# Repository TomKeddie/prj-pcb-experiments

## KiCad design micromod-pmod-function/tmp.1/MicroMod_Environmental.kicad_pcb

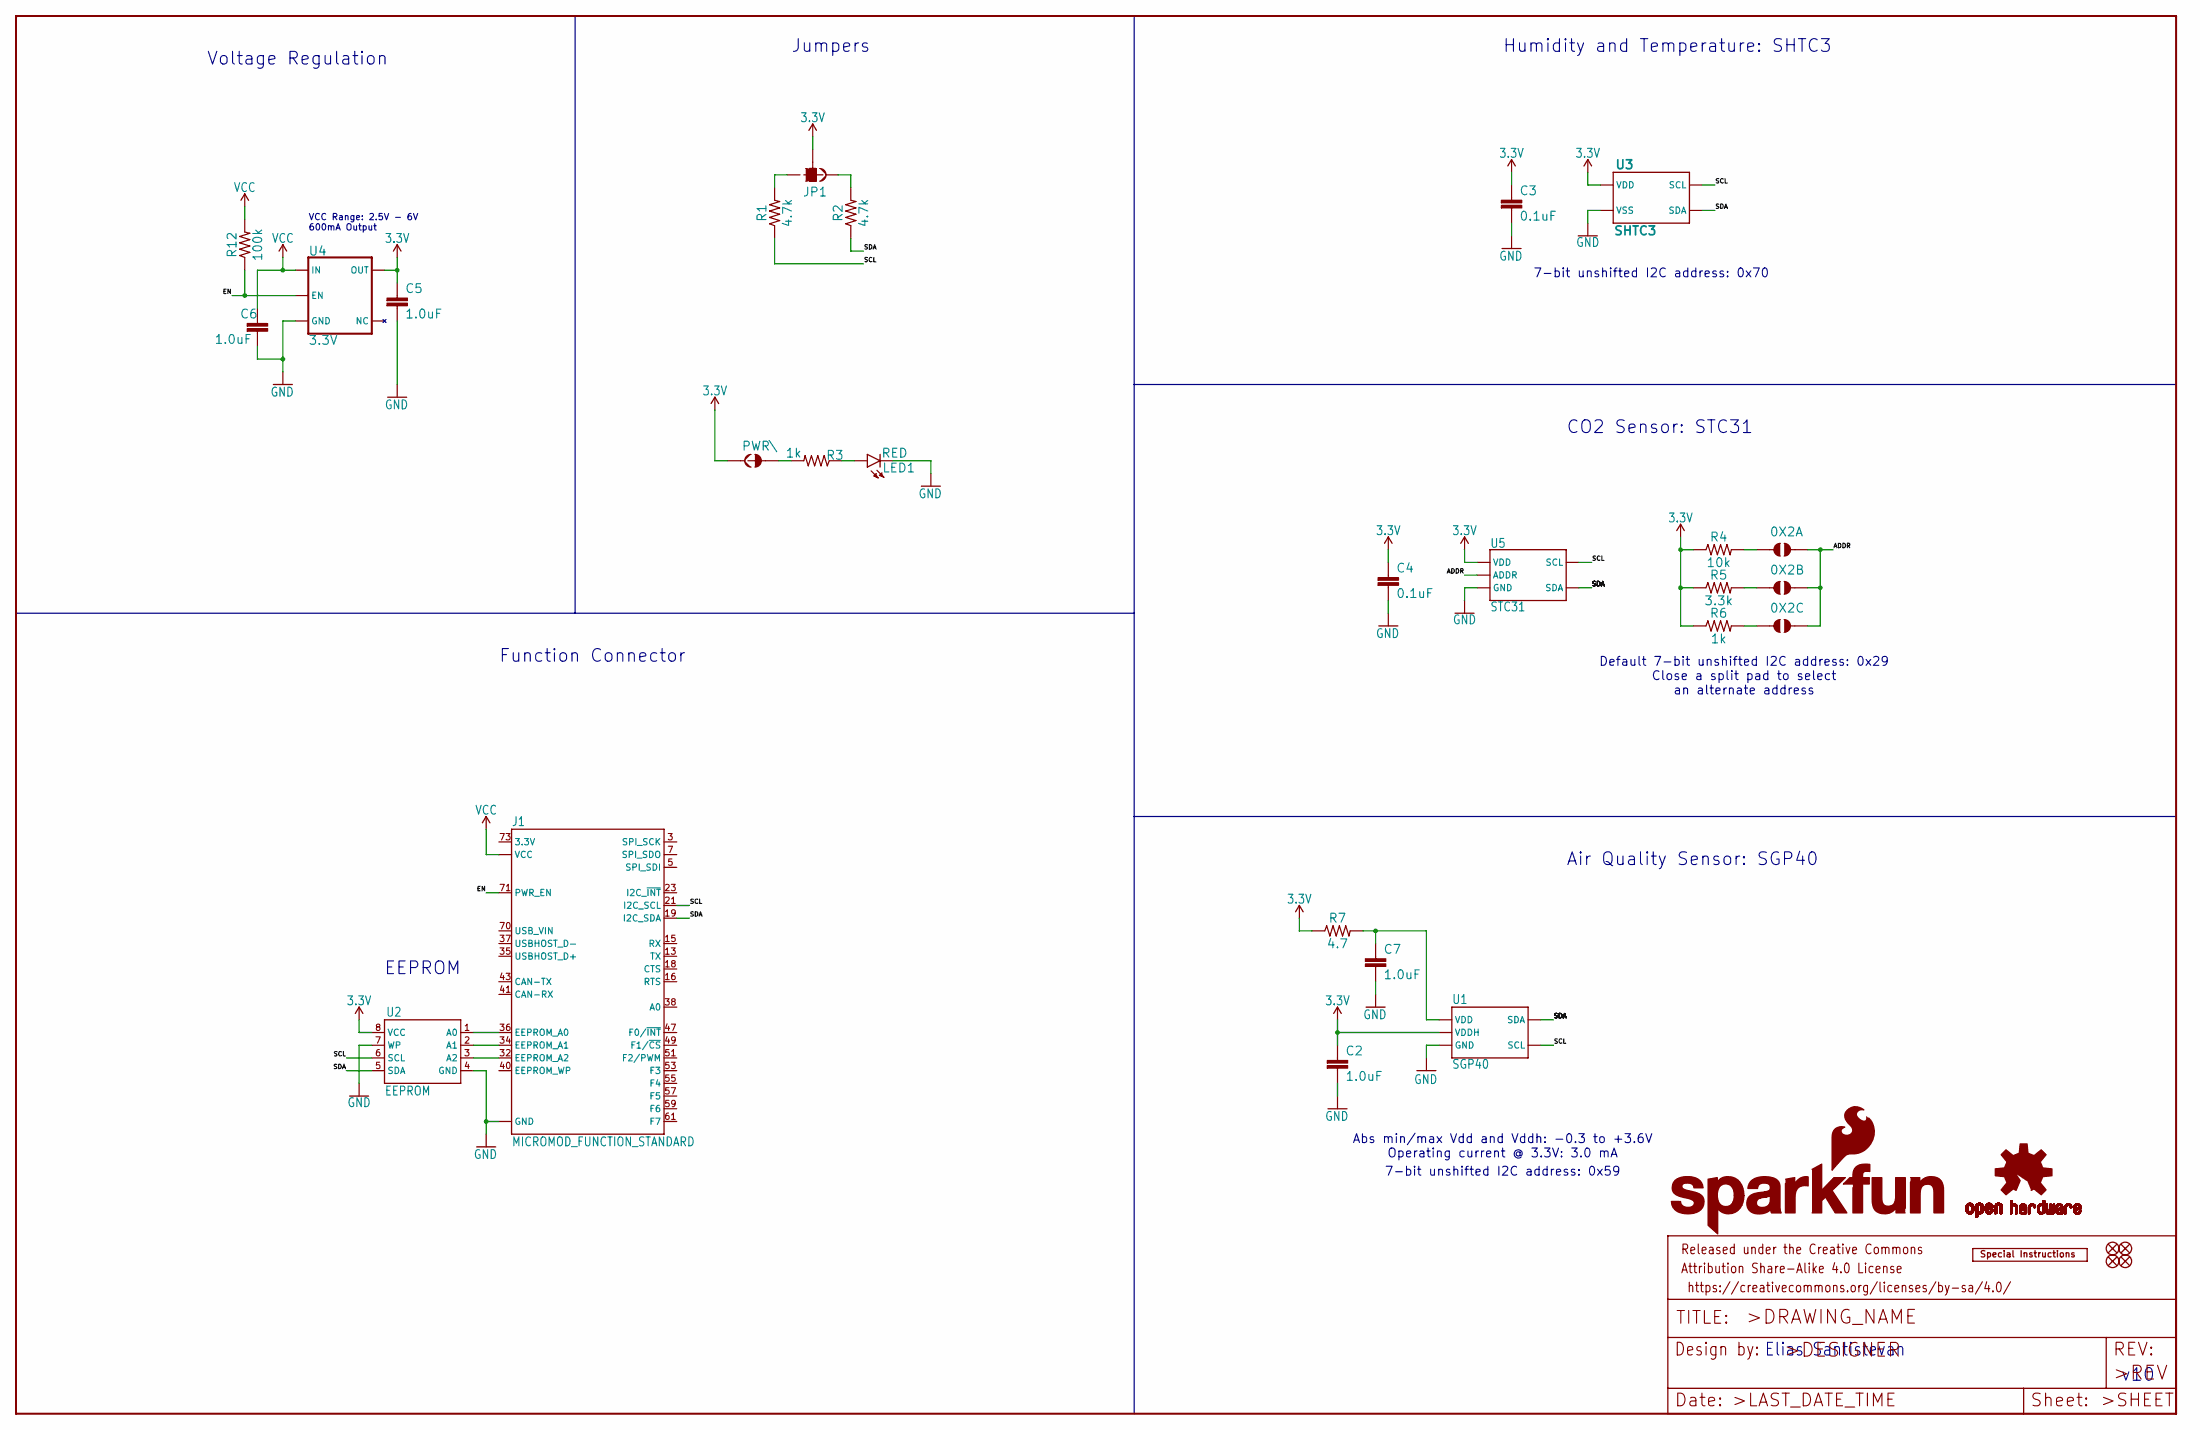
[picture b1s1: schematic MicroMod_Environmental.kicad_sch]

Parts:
0X2A, 0X2B, 0X2C: JUMPER-SMT_2_NO_SILK; SMT-JUMPER_2_NO_SILK
C2, C5, C6, C7: 1.0uF; 0603
C3, C4: 0.1uF; 0603
FD1, FD2, FD3, FD4: FIDUCIAL1X2; FIDUCIAL-1X2
FRAME1: FRAME-LEDGER; CREATIVE_COMMONS
J1: MICROMOD_FUNCTION_STANDARD; M.2-CARD-E-22_FUNCTION_STANDARD
JP1: JUMPER-SMT_3_2-NC_TRACE_SILK; SMT-JUMPER_3_2-NC_TRACE_SILK
LED1: RED; LED-0603
LOGO1: SFE_LOGO_NAME_FLAME.2_INCH; SFE_LOGO_NAME_FLAME_.2
LOGO2: OSHW-LOGOS; OSHW-LOGO-S
LOGO3: SPECIAL_INSTRUCTIONS-ORDERING; ORDERING_INSTRUCTIONS
PWR\: JUMPER-SMT_2_NC_TRACE_SILK; SMT-JUMPER_2_NC_TRACE_SILK
R1, R2: 4.7k; 0603
R3, R6: 1k; 0603
R4: 10k; 0603
R5: 3.3k; 0603
R7: 4.7; 0603
R12: 100k; 0603
U1: SGP40
U2: EEPROM; SO08
U3: SHTC3
U4: 3.3V; SOT23-5
U5: STC31

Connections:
3.3V: C2.1, C3.1, C4.1, C5.1, JP1.2, PWR\.2, R4.1, R5.1, R6.1, R7.1, U1.5 (VDDH), U2.8 (VCC), U3.1 (VDD), U4.5 (OUT), U5.6 (VDD)
A0: J1.36 (EEPROM_A0), U2.1 (A0)
A1: J1.34 (EEPROM_A1), U2.2 (A1)
A2: J1.32 (EEPROM_A2), U2.3 (A2)
ADDR: 0X2A.2, 0X2B.2, 0X2C.2, U5.3 (ADDR)
EN: J1.71 (PWR_EN), R12.1, U4.3 (EN)
GND: C2.2, C3.2, C4.2, C5.2, C6.2, C7.2, J1.1 (GND), J1.33 (GND), J1.39 (GND), J1.45 (GND), J1.75 (GND), J1.GND1 (GND), J1.GND2 (GND), J1.GND3 (GND), J1.GND4 (GND), J1.GND5 (GND), J1.GND6 (GND), LED1.C, U1.2 (GND), U1.4 (GND), U1.DIEPAD (GND), U2.4 (GND), U2.7 (WP), U3.4 (VSS), U3.5 (VSS), U4.2 (GND), U5.1 (GND), U5.5 (GND), U5.9 (GND), U5.11 (GND), U5.DIEPAD (GND)
unnamed: PWR\.1, R3.2
unnamed: C7.1, R7.2, U1.1 (VDD)
unnamed: JP1.3, R1.2
unnamed: JP1.1, R2.2
unnamed: 0X2A.1, R4.2
unnamed: 0X2B.1, R5.2
unnamed: 0X2C.1, R6.2
unnamed: LED1.A, R3.1
SCL: J1.21 (I2C_SCL), R1.1, U1.6 (SCL), U2.6 (SCL), U3.2 (SCL), U5.4 (SCL)
SDA: J1.19 (I2C_SDA), R2.1, U1.3 (SDA), U2.5 (SDA), U3.3 (SDA), U5.7 (SDA)
VCC: C6.1, J1.72 (VCC), J1.74 (VCC), R12.2, U4.1 (IN)

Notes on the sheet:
Humidity and Temperature: SHTC3
Abs min/max Vdd and Vddh: -0.3 to +3.6V Operating current @ 3.3V: 3.0 mA
EEPROM
Function Connector
Jumpers
v10
Default 7-bit unshifted I2C address: 0x29 Close a split pad to select an alternate address
Elias Santistevan
CO2 Sensor: STC31
Air Quality Sensor: SGP40
7-bit unshifted I2C address: 0x70
Voltage Regulation
VCC Range: 2.5V - 6V 600mA Output
7-bit unshifted I2C address: 0x59

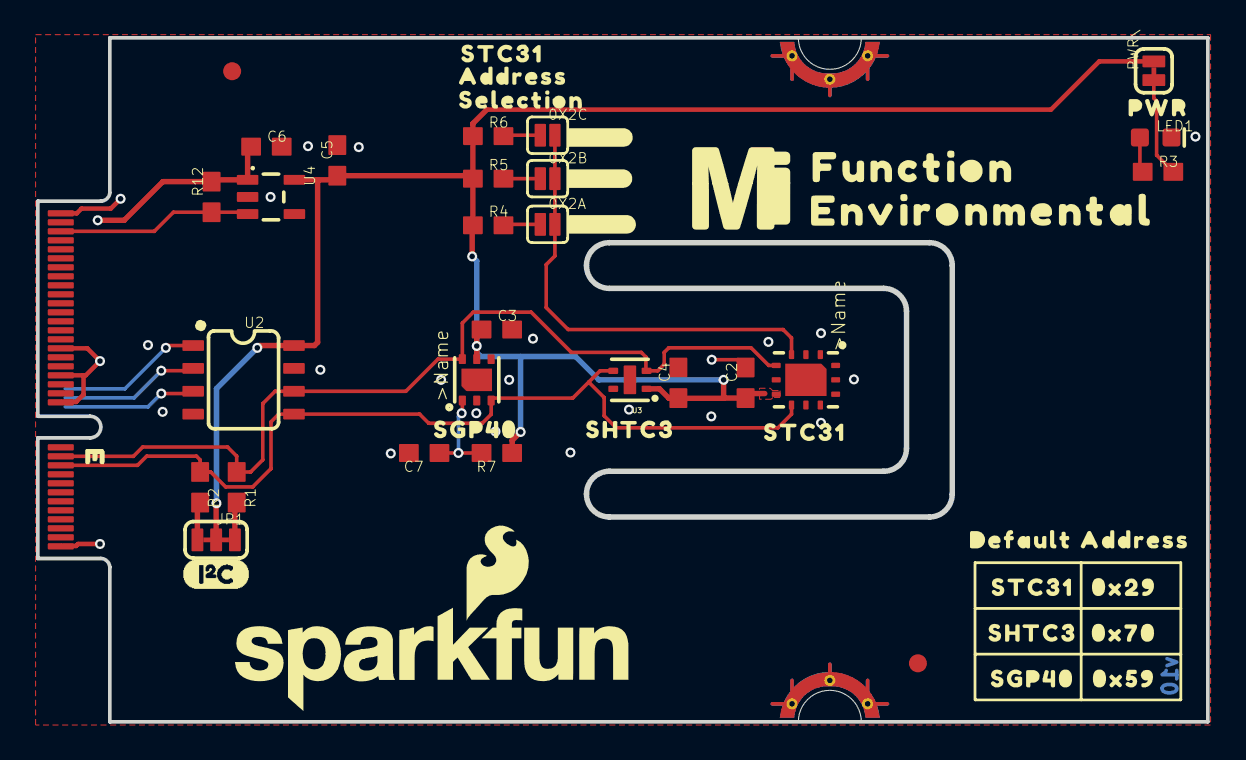
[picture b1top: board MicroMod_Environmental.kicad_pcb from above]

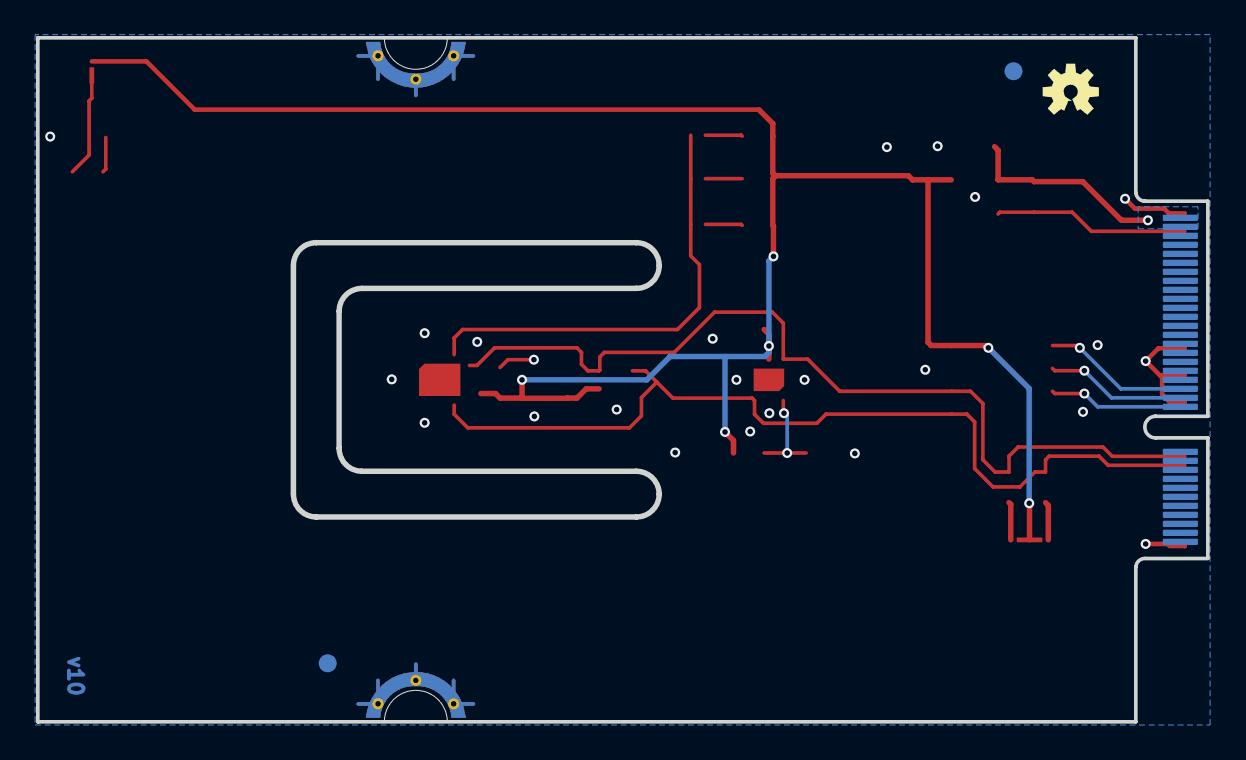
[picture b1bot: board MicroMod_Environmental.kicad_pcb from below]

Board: 2 copper layers, 64.9 x 37.9 mm, 56 parts (3 on the bottom side), 18 nets.

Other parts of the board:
U$1: #0X2A#21
U$2: #0X2B#21
U$3: #0X2C#21
U$4: PWR321541
U$5: FUNCTION524
U$6: ENVIRONMENTAL526
U$7: MICROMOD_MI_LOGO_1
U$8: I2C
U$9, U$15: ADDRESS40313505
U$10: 0X2940313520
U$11, U$18: SGP40313503
U$12, U$17: SHTC3501
U$13, U$16, U$22: STC313502
U$14: DEFAULT40313504
U$19: 0X5940313520
U$20: 0X7040313520
U$21: SELECTION40313506

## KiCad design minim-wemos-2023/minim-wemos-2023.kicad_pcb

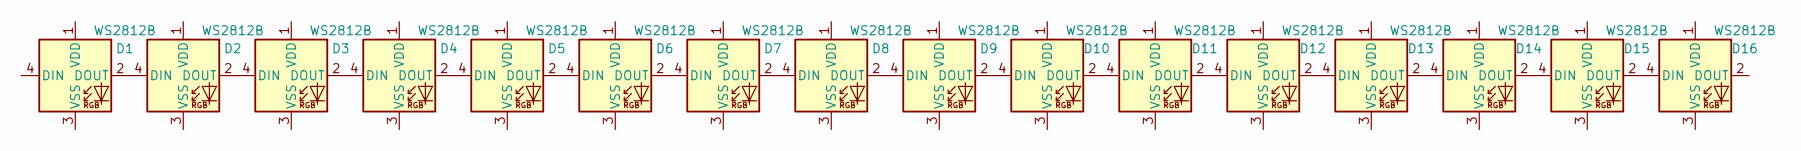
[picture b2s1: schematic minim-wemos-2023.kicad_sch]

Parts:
D1, D2, D3, D4, D5, D6, D7, D8, D9, D10, D11, D12, D13, D14, D15, D16: WS2812B; LED_WS2812B_PLCC4_5.0x5.0mm_P3.2mm; LCSC C2843785

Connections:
unnamed: D1.2 (DOUT), D2.4 (DIN)
unnamed: D2.2 (DOUT), D3.4 (DIN)
unnamed: D3.2 (DOUT), D4.4 (DIN)
unnamed: D4.2 (DOUT), D5.4 (DIN)
unnamed: D5.2 (DOUT), D6.4 (DIN)
unnamed: D6.2 (DOUT), D7.4 (DIN)
unnamed: D7.2 (DOUT), D8.4 (DIN)
unnamed: D8.2 (DOUT), D9.4 (DIN)
unnamed: D9.2 (DOUT), D10.4 (DIN)
unnamed: D10.2 (DOUT), D11.4 (DIN)
unnamed: D11.2 (DOUT), D12.4 (DIN)
unnamed: D12.2 (DOUT), D13.4 (DIN)
unnamed: D13.2 (DOUT), D14.4 (DIN)
unnamed: D14.2 (DOUT), D15.4 (DIN)
unnamed: D15.2 (DOUT), D16.4 (DIN)

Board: 2 copper layers, 16 parts (0 on the bottom side), 15 nets, no tracks yet.

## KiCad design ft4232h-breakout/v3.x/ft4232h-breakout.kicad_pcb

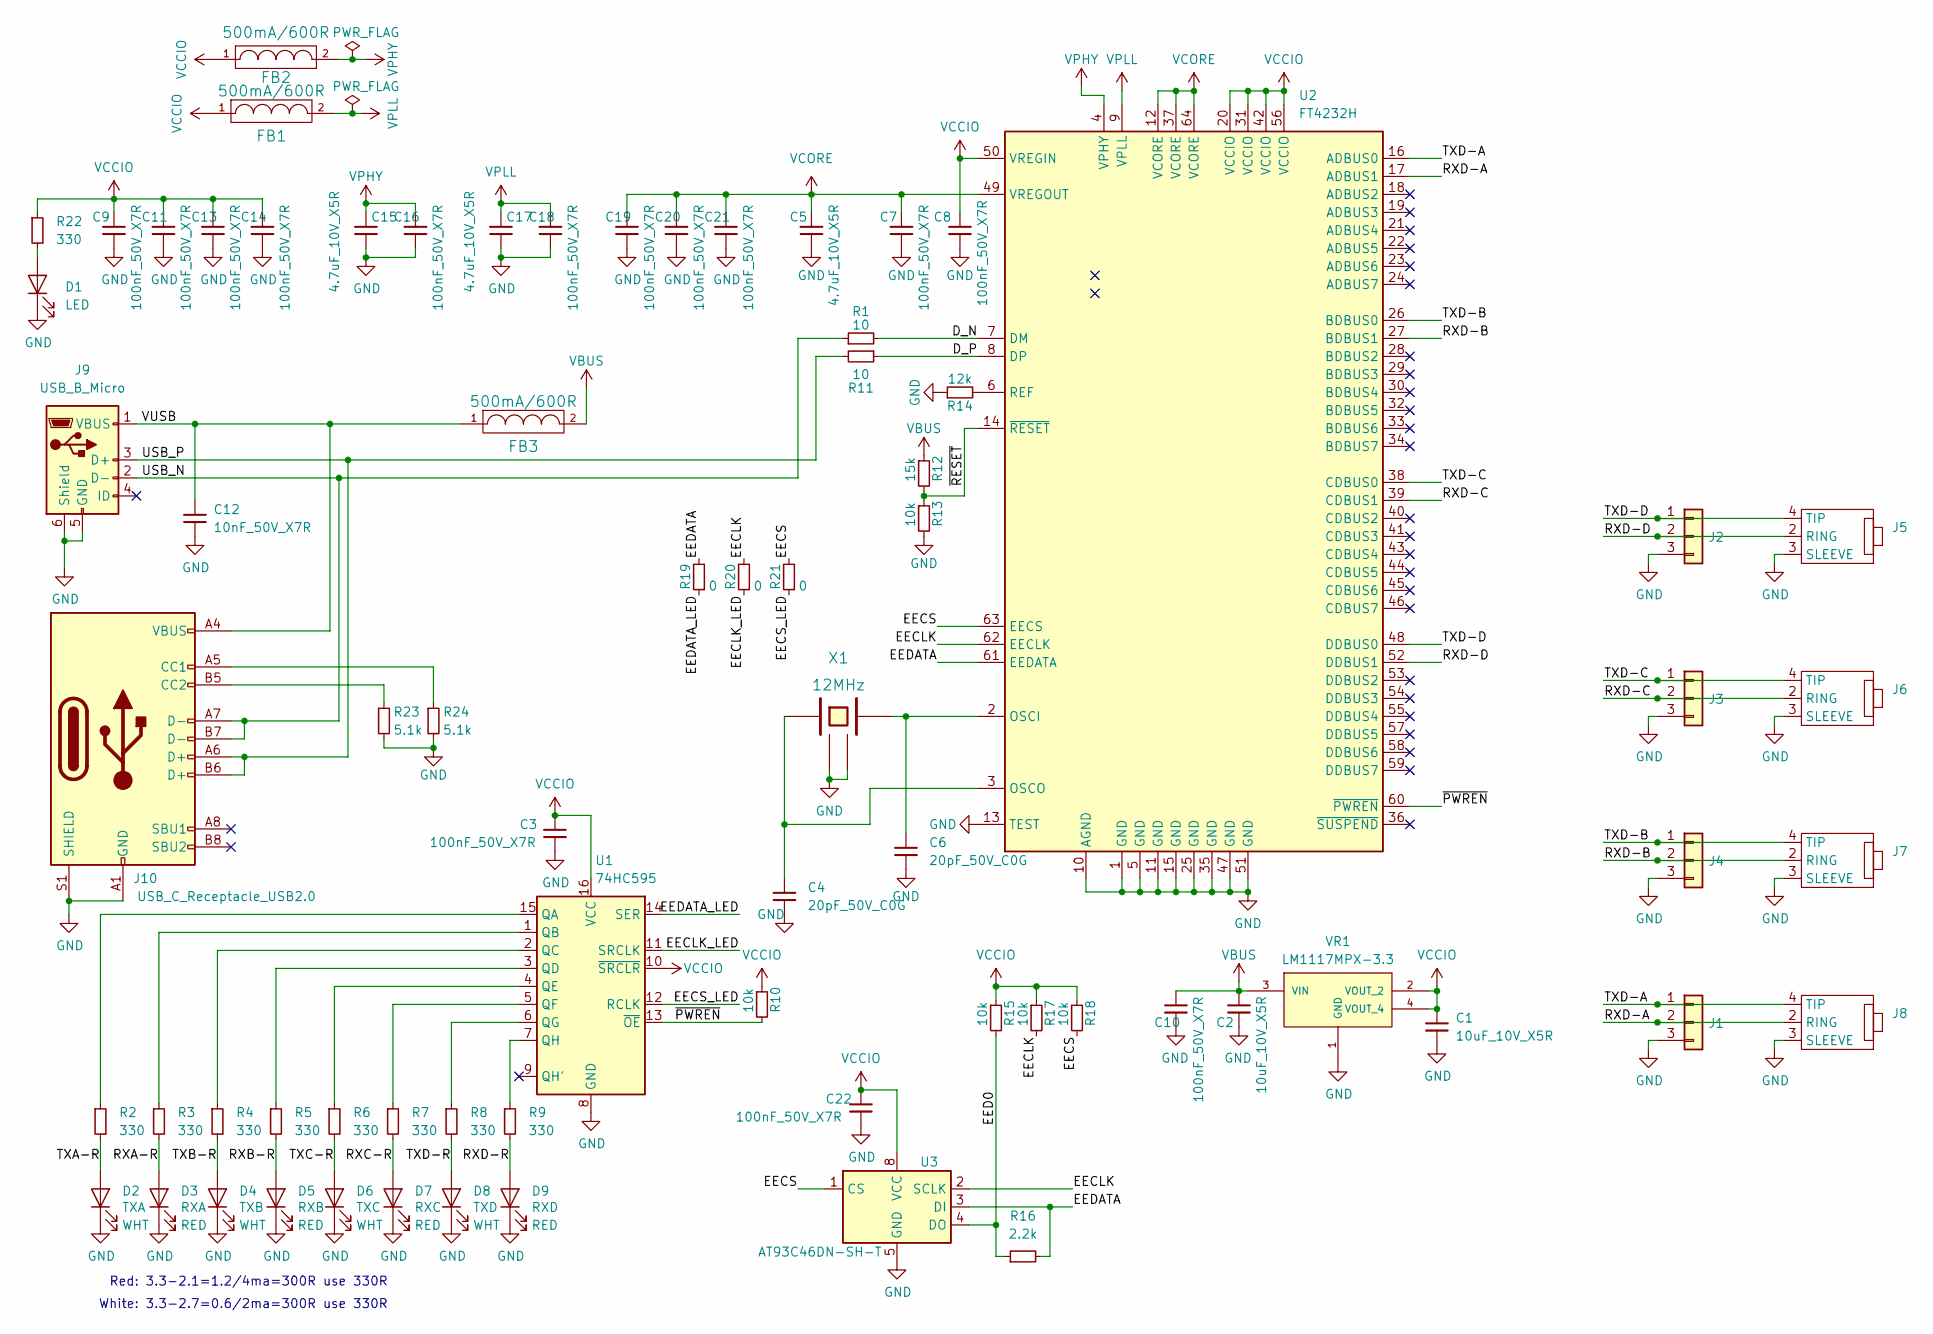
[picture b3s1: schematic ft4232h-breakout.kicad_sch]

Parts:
C1, C2: 10uF_10V_X5R; C_0603_1608Metric; MFGPN CL10A106KP8NNNC; LCSC C19702
C3, C7, C8, C9, C10, C11, C13, C14, C16, C18, C19, C20, C21, C22: 100nF_50V_X7R; C_0402_1005Metric; MFGPN CL05B104KB54PNC; LCSC C307331
C4, C6: 20pF_50V_C0G; C_0402_1005Metric; MFGPN 0402CG200J500NT; LCSC C1554
C5, C15, C17: 4.7uF_10V_X5R; C_0402_1005Metric; MFGPN CL05A475MP5NRNC; LCSC C23733
C12: 10nF_50V_X7R; C_0402_1005Metric; MFGPN CL05B103KB5NNNC; LCSC C15195
D1: LED; LED_0603_1608Metric; LCSC C2290
D2: TXA; LED_0603_1608Metric; LCSC C2290
D3: RXA; LED_0603_1608Metric; LCSC C2290
D4: TXB; LED_0603_1608Metric; LCSC C2290
D5: RXB; LED_0603_1608Metric; LCSC C2290
D6: TXC; LED_0603_1608Metric; LCSC C2290
D7: RXC; LED_0603_1608Metric; LCSC C2290
D8: TXD; LED_0603_1608Metric; LCSC C2290
D9: RXD; LED_0603_1608Metric; LCSC C2290
FB1, FB2, FB3: 500mA/600R; C_0805_2012Metric; LCSC C1017
J1, J2, J3, J4: Conn_01x03; PinHeader_1x03_P2.54mm_Horizontal; LCSC C492411
J5, J6, J7, J8: JLCPCB_3.5MM_SOCKET_C18166; MPN PJ-3200; LCSC C18166
J9: USB_B_Micro; USB_B_Micro_LCSC_C10418; LCSC C10418
J10: USB_C_Receptacle_USB2.0; USB_C_Receptacle_LCSC_C165948; LCSC C165948
R1, R11: 10; R_0402_1005Metric; MFGPN 0402WGF100JTCE; LCSC C25077
R2, R3, R4, R5, R6, R7, R8, R9, R22: 330; R_0402_1005Metric; MFGPN 0402WGF3300TCE; LCSC C25104
R10, R13, R15, R17, R18: 10k; R_0402_1005Metric; MFGPN 0402WGF1002TCE; LCSC C25744
R12: 15k; R_0402_1005Metric; MFGPN 0402WGF1502TCE; LCSC C25756
R14: 12k; R_0402_1005Metric; MFGPN 0402WGF1202TCE; LCSC C25752
R16: 2.2k; R_0402_1005Metric; MFGPN 0402WGF2201TCE; LCSC C25879
R19, R20, R21: 0; R_0402_1005Metric; MFGPN 0402WGF0000TCE; LCSC C17168
R23, R24: 5.1k; R_0402_1005Metric; MFGPN 0402WGF5101TCE; LCSC C25905
U1: 74HC595; SOIC-16_4.55x10.3mm_P1.27mm; LCSC C5947
U2: FT4232H; TQFP-64_10x10mm_P0.5mm; LCSC DNP
U3: AT93C46DN-SH-T; SO-8_3.9x4.9mm_P1.27mm; LCSC C6499
VR1: LM1117MPX-3.3; VREG_LM1117MPX-3.3; PARTREV O; LCSC C6186
X1: 12MHz; Crystal_SMD_3225-4Pin_3.2x2.5mm; LCSC C9002

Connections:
/D_N: R1.2, U2.7 (DM)
/D_P: R11.1, U2.8 (DP)
/EECLK: R17.2, R20.2, U2.62 (EECLK), U3.2 (SCLK)
/EECLK_LED: R20.1, U1.11 (SRCLK)
/EECS: R18.2, R21.2, U2.63 (EECS), U3.1 (CS)
/EECS_LED: R21.1, U1.12 (RCLK)
/EED0: R15.2, R16.1, U3.4 (DO)
/EEDATA: R16.2, R19.2, U2.61 (EEDATA), U3.3 (DI)
/EEDATA_LED: R19.1, U1.14 (SER)
/RXA-R: D3.2 (A), R3.2
/RXB-R: D5.2 (A), R5.2
/RXC-R: D7.2 (A), R7.2
/RXD-A: J1.2, J8.2 (RING), U2.17 (ADBUS1)
/RXD-B: J4.2, J7.2 (RING), U2.27 (BDBUS1)
/RXD-C: J3.2, J6.2 (RING), U2.39 (CDBUS1)
/RXD-D: J2.2, J5.2 (RING), U2.52 (DDBUS1)
/RXD-R: D9.2 (A), R9.2
/TXA-R: D2.2 (A), R2.2
/TXB-R: D4.2 (A), R4.2
/TXC-R: D6.2 (A), R6.2
/TXD-A: J1.1, J8.4 (TIP), U2.16 (ADBUS0)
/TXD-B: J4.1, J7.4 (TIP), U2.26 (BDBUS0)
/TXD-C: J3.1, J6.4 (TIP), U2.38 (CDBUS0)
/TXD-D: J2.1, J5.4 (TIP), U2.48 (DDBUS0)
/TXD-R: D8.2 (A), R8.2
/USB_N: J9.2 (D-), J10.A7 (D-), J10.B7 (D-), R1.1
/USB_P: J9.3 (D+), J10.A6 (D+), J10.B6 (D+), R11.2
/VUSB: C12.1, FB3.1, J9.1 (VBUS), J10.A4 (VBUS), J10.A9 (VBUS), J10.B4 (VBUS), J10.B9 (VBUS)
/~PWREN: R10.2, U1.13 (~OE), U2.60 (~PWREN)
/~RESET: R12.2, R13.1, U2.14 (~RESET)
GND: C1.2, C2.2, C3.1, C4.2, C5.2, C6.2, C7.1, C8.1, C9.1, C10.1, C11.1, C12.2, C13.1, C14.1, C15.2, C16.1, C17.2, C18.1, C19.1, C20.1, C21.1, C22.1, D1.1 (K), D2.1 (K), D3.1 (K), D4.1 (K), D5.1 (K), D6.1 (K), D7.1 (K), D8.1 (K), D9.1 (K), J1.3, J2.3, J3.3, J4.3, J5.3 (SLEEVE), J6.3 (SLEEVE), J7.3 (SLEEVE), J8.3 (SLEEVE), J9.5 (GND), J9.6 (Shield), J10.A1 (GND), J10.A12 (GND), J10.B1 (GND), J10.B12 (GND), J10.S1 (SHIELD), R13.2, R14.1, R23.2, R24.2, U1.8 (GND), U2.1 (GND), U2.5 (GND), U2.10 (AGND), U2.11 (GND), U2.13 (TEST), U2.15 (GND), U2.25 (GND), U2.35 (GND), U2.47 (GND), U2.51 (GND), U3.5 (GND), VR1.1 (GND), X1.2 (GND), X1.4 (GND)
unnamed: C4.1, U2.3 (OSCO), X1.1
unnamed: C6.1, U2.2 (OSCI), X1.3
unnamed: D1.2 (A), R22.2
unnamed: J10.A5 (CC1), R24.1
unnamed: J10.B5 (CC2), R23.1
unnamed: R2.1, U1.15 (QA)
unnamed: R3.1, U1.1 (QB)
unnamed: R4.1, U1.2 (QC)
unnamed: R5.1, U1.3 (QD)
unnamed: R6.1, U1.4 (QE)
unnamed: R7.1, U1.5 (QF)
unnamed: R8.1, U1.6 (QG)
unnamed: R9.1, U1.7 (QH)
unnamed: R14.2, U2.6 (REF)
VBUS: C2.1, C10.2, FB3.2, R12.1, VR1.3 (VIN)
VCCIO: C1.1, C3.2, C8.2, C9.2, C11.2, C13.2, C14.2, C22.2, FB1.1, FB2.1, R10.1, R15.1, R17.1, R18.1, R22.1, U1.10 (~SRCLR), U1.16 (VCC), U2.20 (VCCIO), U2.31 (VCCIO), U2.42 (VCCIO), U2.50 (VREGIN), U2.56 (VCCIO), U3.8 (VCC), VR1.2 (VOUT_2), VR1.4 (VOUT_4)
VCORE: C5.1, C7.2, C19.2, C20.2, C21.2, U2.12 (VCORE), U2.37 (VCORE), U2.49 (VREGOUT), U2.64 (VCORE)
VPHY: C15.1, C16.2, FB2.2, U2.4 (VPHY)
VPLL: C17.1, C18.2, FB1.2, U2.9 (VPLL)

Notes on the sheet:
Red: 3.3-2.1=1.2/4ma=300R use 330R
White: 3.3-2.7=0.6/2ma=300R use 330R

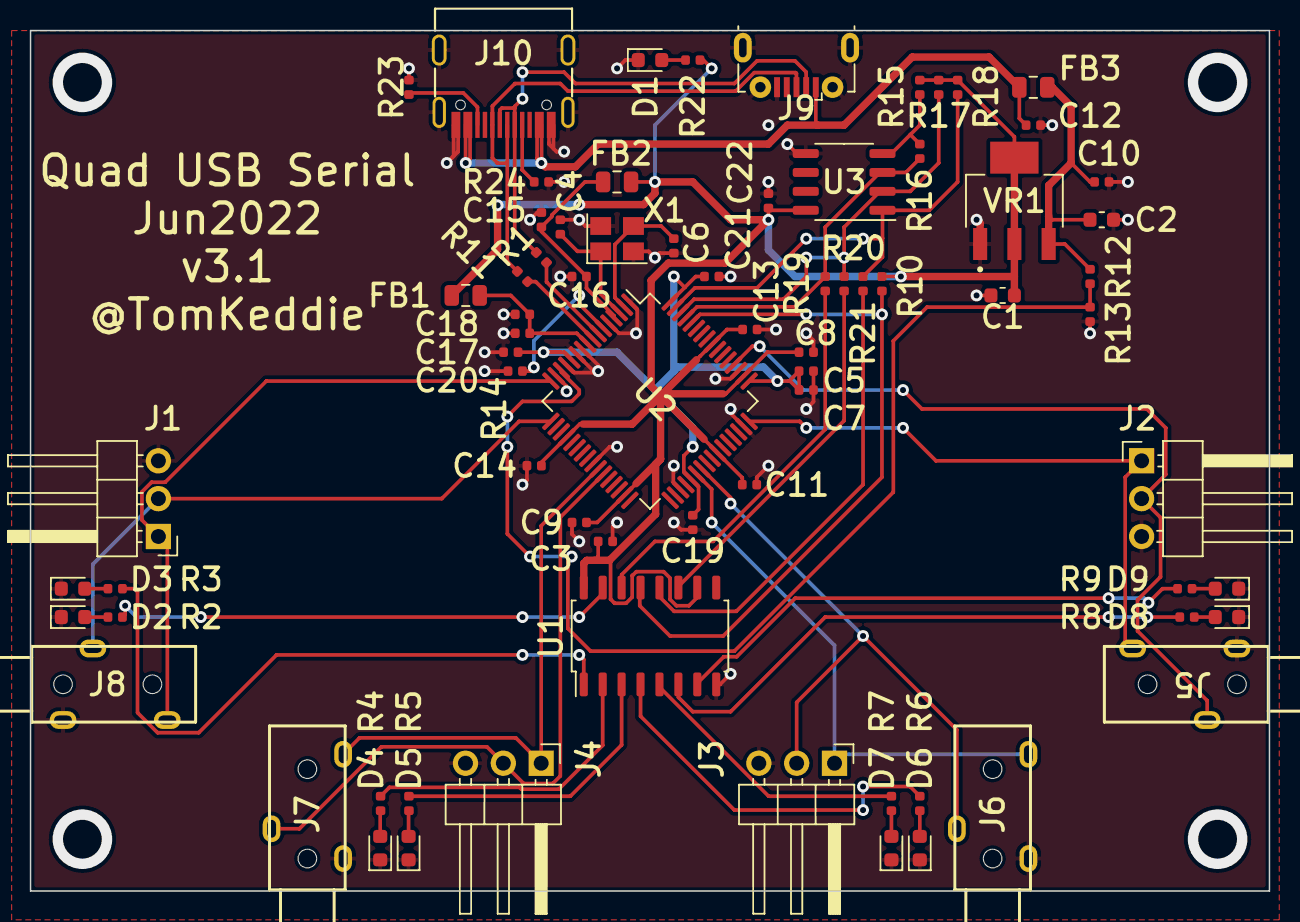
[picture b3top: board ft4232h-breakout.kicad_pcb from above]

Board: 2 copper layers, 83.2 x 57.8 mm, 73 parts (0 on the bottom side), 50 nets.

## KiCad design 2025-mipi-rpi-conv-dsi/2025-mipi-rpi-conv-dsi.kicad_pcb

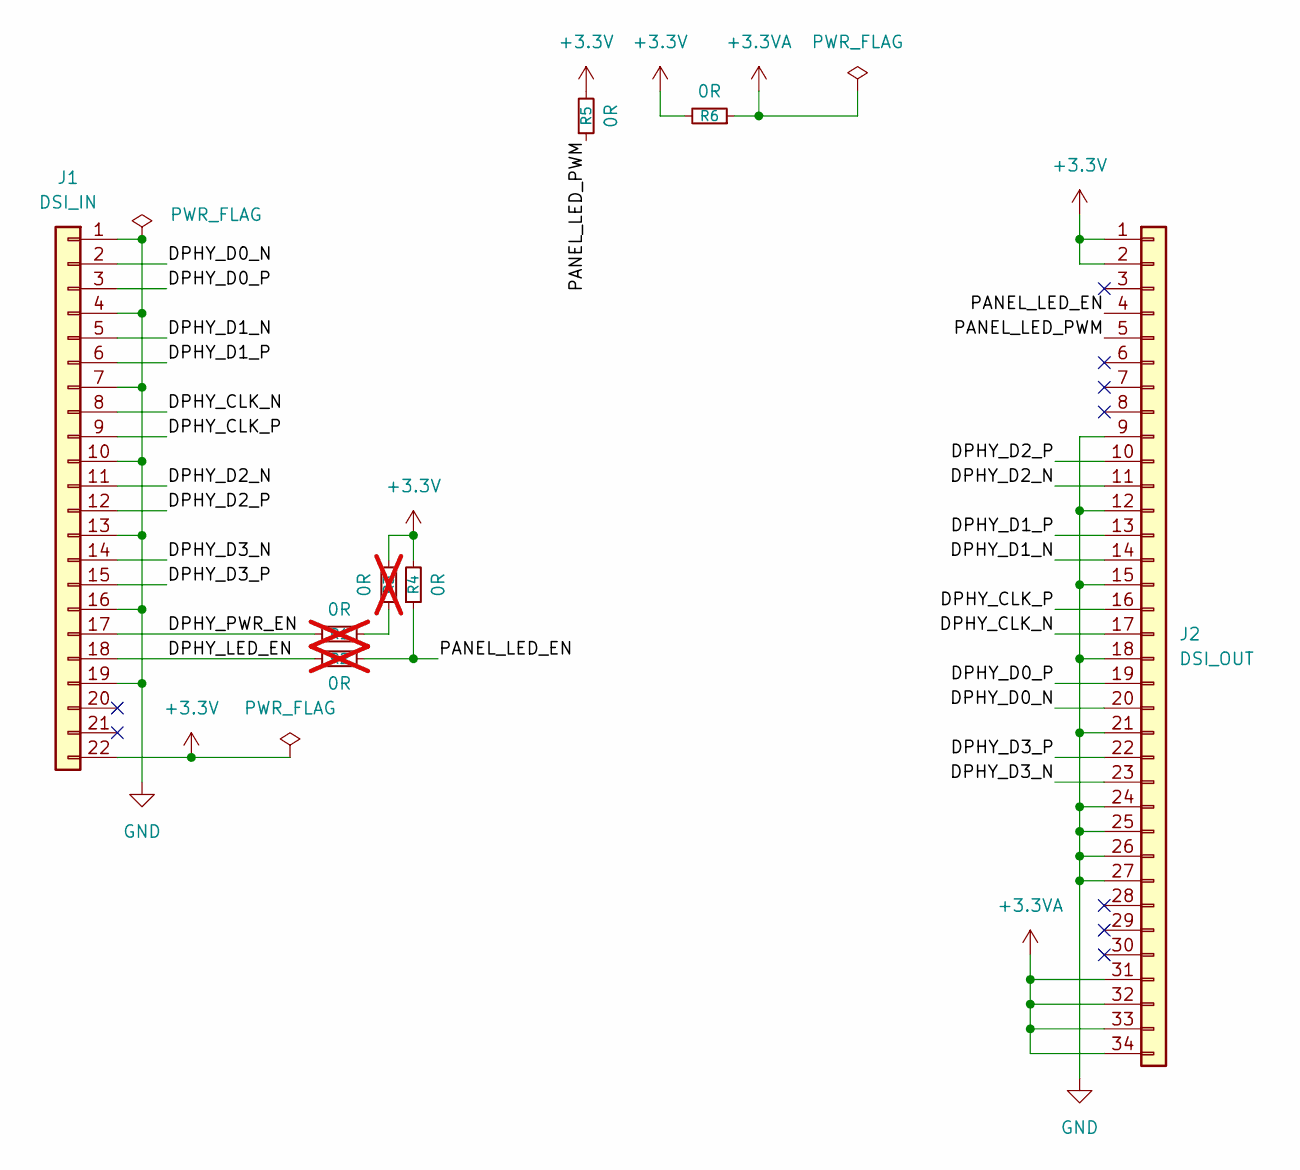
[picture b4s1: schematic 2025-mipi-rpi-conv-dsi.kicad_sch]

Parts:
J1: DSI_IN; AliExpress_1x22_P0.5mm_Horizontal_Drawer
J2: DSI_OUT; AliExpress_1x34_P0.5mm_Horizontal_Drawer
R1, R2, R3: 0R; R_0603_1608Metric; not fitted
R4, R5, R6: 0R; R_0603_1608Metric

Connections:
+3.3V: J1.22, J2.1, J2.2, R3.2, R4.2, R5.2, R6.2
+3.3VA: J2.31, J2.32, J2.33, J2.34, R6.1
/DPHY_CLK_N: J1.8, J2.17
/DPHY_CLK_P: J1.9, J2.16
/DPHY_D0_N: J1.2, J2.20
/DPHY_D0_P: J1.3, J2.19
/DPHY_D1_N: J1.5, J2.14
/DPHY_D1_P: J1.6, J2.13
/DPHY_D2_N: J1.11, J2.11
/DPHY_D2_P: J1.12, J2.10
/DPHY_D3_N: J1.14, J2.23
/DPHY_D3_P: J1.15, J2.22
/DPHY_LED_EN: J1.18, R2.1
/DPHY_PWR_EN: J1.17, R1.1
/PANEL_LED_EN: J2.4, R2.2, R4.1
/PANEL_LED_PWM: J2.5, R5.1
GND: J1.1, J1.4, J1.7, J1.10, J1.13, J1.16, J1.19, J2.9, J2.12, J2.15, J2.18, J2.21, J2.24, J2.25, J2.26, J2.27
unnamed: R1.2, R3.1

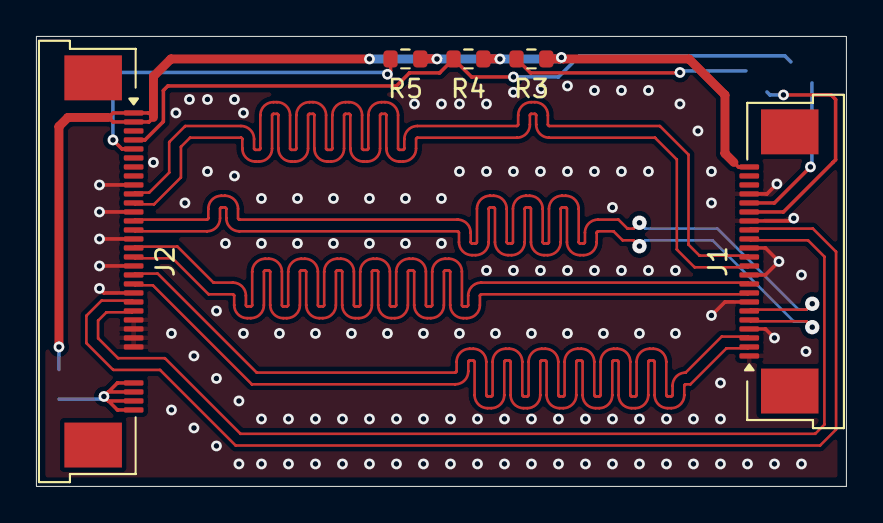
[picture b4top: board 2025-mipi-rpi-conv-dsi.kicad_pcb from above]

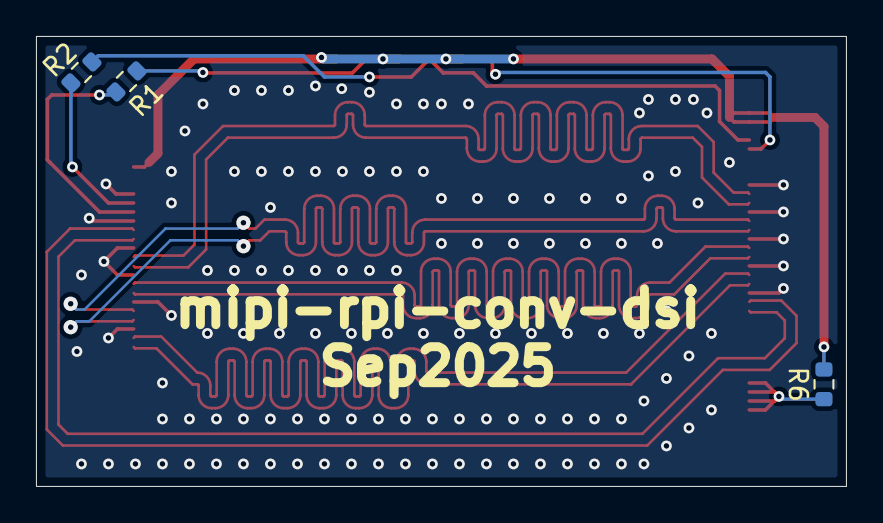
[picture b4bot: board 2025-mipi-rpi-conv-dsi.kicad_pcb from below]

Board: 2 copper layers, 45.0 x 25.0 mm, 8 parts (3 on the bottom side), 18 nets.

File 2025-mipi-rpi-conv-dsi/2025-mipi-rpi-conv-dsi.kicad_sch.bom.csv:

"Value","Designator","Footprint","LCSC"
"0R,DSI_IN,DSI_OUT","J1,J2,R1-R6","lib:AliExpress_1x22_P0.5mm_Horizontal_Drawer,lib:AliExpress_1x34_P0.5mm_Horizontal_Drawer,lib:R_0603_1608Metric",""

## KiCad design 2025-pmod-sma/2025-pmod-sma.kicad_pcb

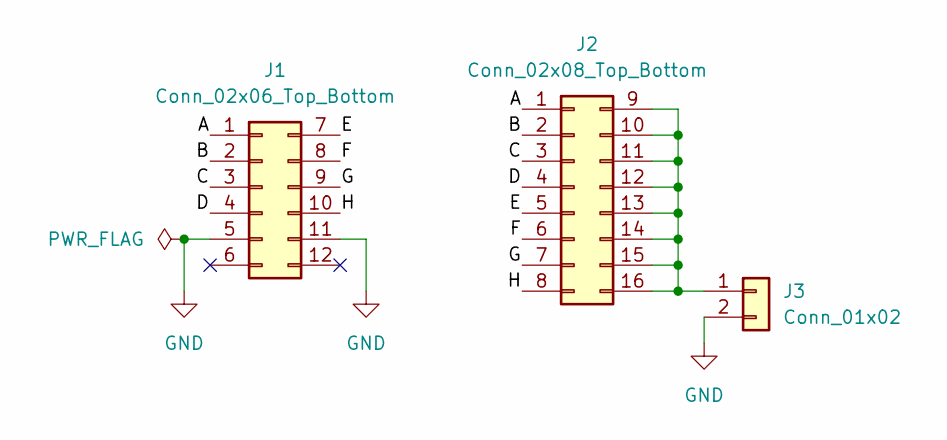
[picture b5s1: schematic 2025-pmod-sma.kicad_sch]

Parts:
J1: Conn_02x06_Top_Bottom; PinHeader_2x06_P2.54mm_Horizontal_Top_Bottom
J2: Conn_02x08_Top_Bottom; PinHeader_2x08_P2.54mm_Vertical_Top_Bottom
J3: Conn_01x02; SMA_Amphenol_901-143_Horizontal

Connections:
/A: J1.1, J2.1
/B: J1.2, J2.2
/C: J1.3, J2.3
/D: J1.4, J2.4
/E: J1.7, J2.5
/F: J1.8, J2.6
/G: J1.9, J2.7
/H: J1.10, J2.8
GND: J1.5, J1.11, J3.2
unnamed: J2.9, J2.10, J2.11, J2.12, J2.13, J2.14, J2.15, J2.16, J3.1

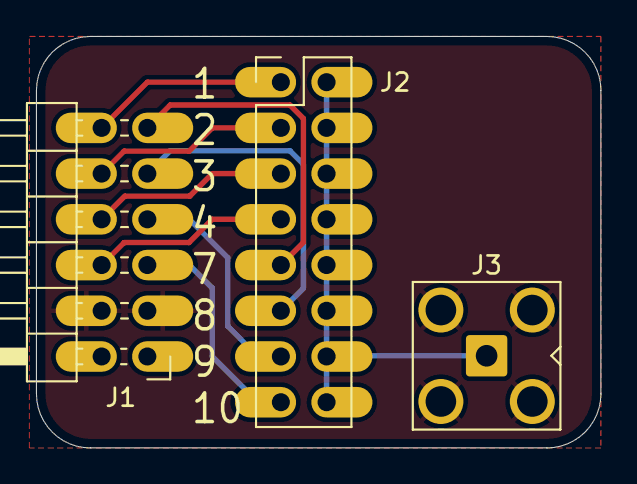
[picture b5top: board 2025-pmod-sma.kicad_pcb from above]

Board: 2 copper layers, 31.4 x 22.9 mm, 3 parts (0 on the bottom side), 10 nets.

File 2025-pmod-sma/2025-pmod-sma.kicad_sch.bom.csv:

"Value","Designator","Footprint","LCSC"
"Conn_01x02,Conn_02x06_Top_Bottom,Conn_02x08_Top_Bottom","J1-J3","lib:PinHeader_2x06_P2.54mm_Horizontal_Top_Bottom,lib:PinHeader_2x08_P2.54mm_Vertical_Top_Bottom,lib:SMA_Amphenol_901-143_Horizontal",""

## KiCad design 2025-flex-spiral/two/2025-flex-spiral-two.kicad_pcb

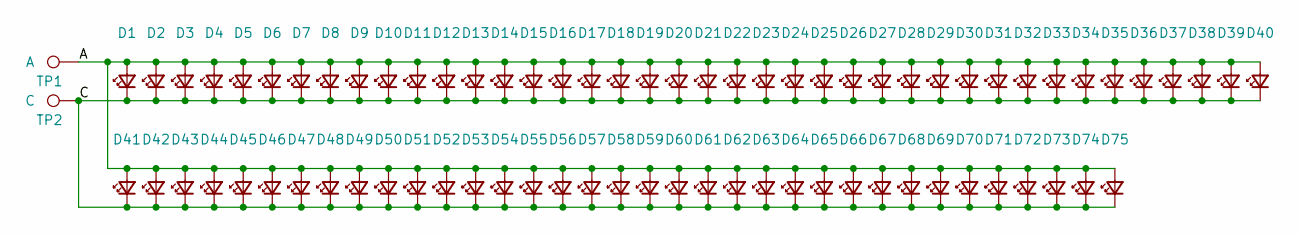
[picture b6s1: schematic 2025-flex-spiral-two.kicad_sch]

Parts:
D1, D2, D3, D4, D5, D6, D7, D8, D9, D10, D11, D12, D13, D14, D15, D16, D17, D18, D19, D20, D21, D22, D23, D24, D25, D26, D27, D28, D29, D30, D31, D32, D33, D34, D35, D36, D37, D38, D39, D40, D41, D42, D43, D44, D45, D46, D47, D48, D49, D50, D51, D52, D53, D54, D55, D56, D57, D58, D59, D60, D61, D62, D63, D64, D65, D66, D67, D68, D69, D70, D71, D72, D73, D74, D75: led_small; LED_0603_1608Metric
TP1: A; TestPoint_Pad_D3.0mm
TP2: C; TestPoint_Pad_D3.0mm

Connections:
/A: D1.2 (A), D2.2 (A), D3.2 (A), D4.2 (A), D5.2 (A), D6.2 (A), D7.2 (A), D8.2 (A), D9.2 (A), D10.2 (A), D11.2 (A), D12.2 (A), D13.2 (A), D14.2 (A), D15.2 (A), D16.2 (A), D17.2 (A), D18.2 (A), D19.2 (A), D20.2 (A), D21.2 (A), D22.2 (A), D23.2 (A), D24.2 (A), D25.2 (A), D26.2 (A), D27.2 (A), D28.2 (A), D29.2 (A), D30.2 (A), D31.2 (A), D32.2 (A), D33.2 (A), D34.2 (A), D35.2 (A), D36.2 (A), D37.2 (A), D38.2 (A), D39.2 (A), D40.2 (A), D41.2 (A), D42.2 (A), D43.2 (A), D44.2 (A), D45.2 (A), D46.2 (A), D47.2 (A), D48.2 (A), D49.2 (A), D50.2 (A), D51.2 (A), D52.2 (A), D53.2 (A), D54.2 (A), D55.2 (A), D56.2 (A), D57.2 (A), D58.2 (A), D59.2 (A), D60.2 (A), D61.2 (A), D62.2 (A), D63.2 (A), D64.2 (A), D65.2 (A), D66.2 (A), D67.2 (A), D68.2 (A), D69.2 (A), D70.2 (A), D71.2 (A), D72.2 (A), D73.2 (A), D74.2 (A), D75.2 (A), TP1.1
/C: D1.1 (K), D2.1 (K), D3.1 (K), D4.1 (K), D5.1 (K), D6.1 (K), D7.1 (K), D8.1 (K), D9.1 (K), D10.1 (K), D11.1 (K), D12.1 (K), D13.1 (K), D14.1 (K), D15.1 (K), D16.1 (K), D17.1 (K), D18.1 (K), D19.1 (K), D20.1 (K), D21.1 (K), D22.1 (K), D23.1 (K), D24.1 (K), D25.1 (K), D26.1 (K), D27.1 (K), D28.1 (K), D29.1 (K), D30.1 (K), D31.1 (K), D32.1 (K), D33.1 (K), D34.1 (K), D35.1 (K), D36.1 (K), D37.1 (K), D38.1 (K), D39.1 (K), D40.1 (K), D41.1 (K), D42.1 (K), D43.1 (K), D44.1 (K), D45.1 (K), D46.1 (K), D47.1 (K), D48.1 (K), D49.1 (K), D50.1 (K), D51.1 (K), D52.1 (K), D53.1 (K), D54.1 (K), D55.1 (K), D56.1 (K), D57.1 (K), D58.1 (K), D59.1 (K), D60.1 (K), D61.1 (K), D62.1 (K), D63.1 (K), D64.1 (K), D65.1 (K), D66.1 (K), D67.1 (K), D68.1 (K), D69.1 (K), D70.1 (K), D71.1 (K), D72.1 (K), D73.1 (K), D74.1 (K), D75.1 (K), TP2.1

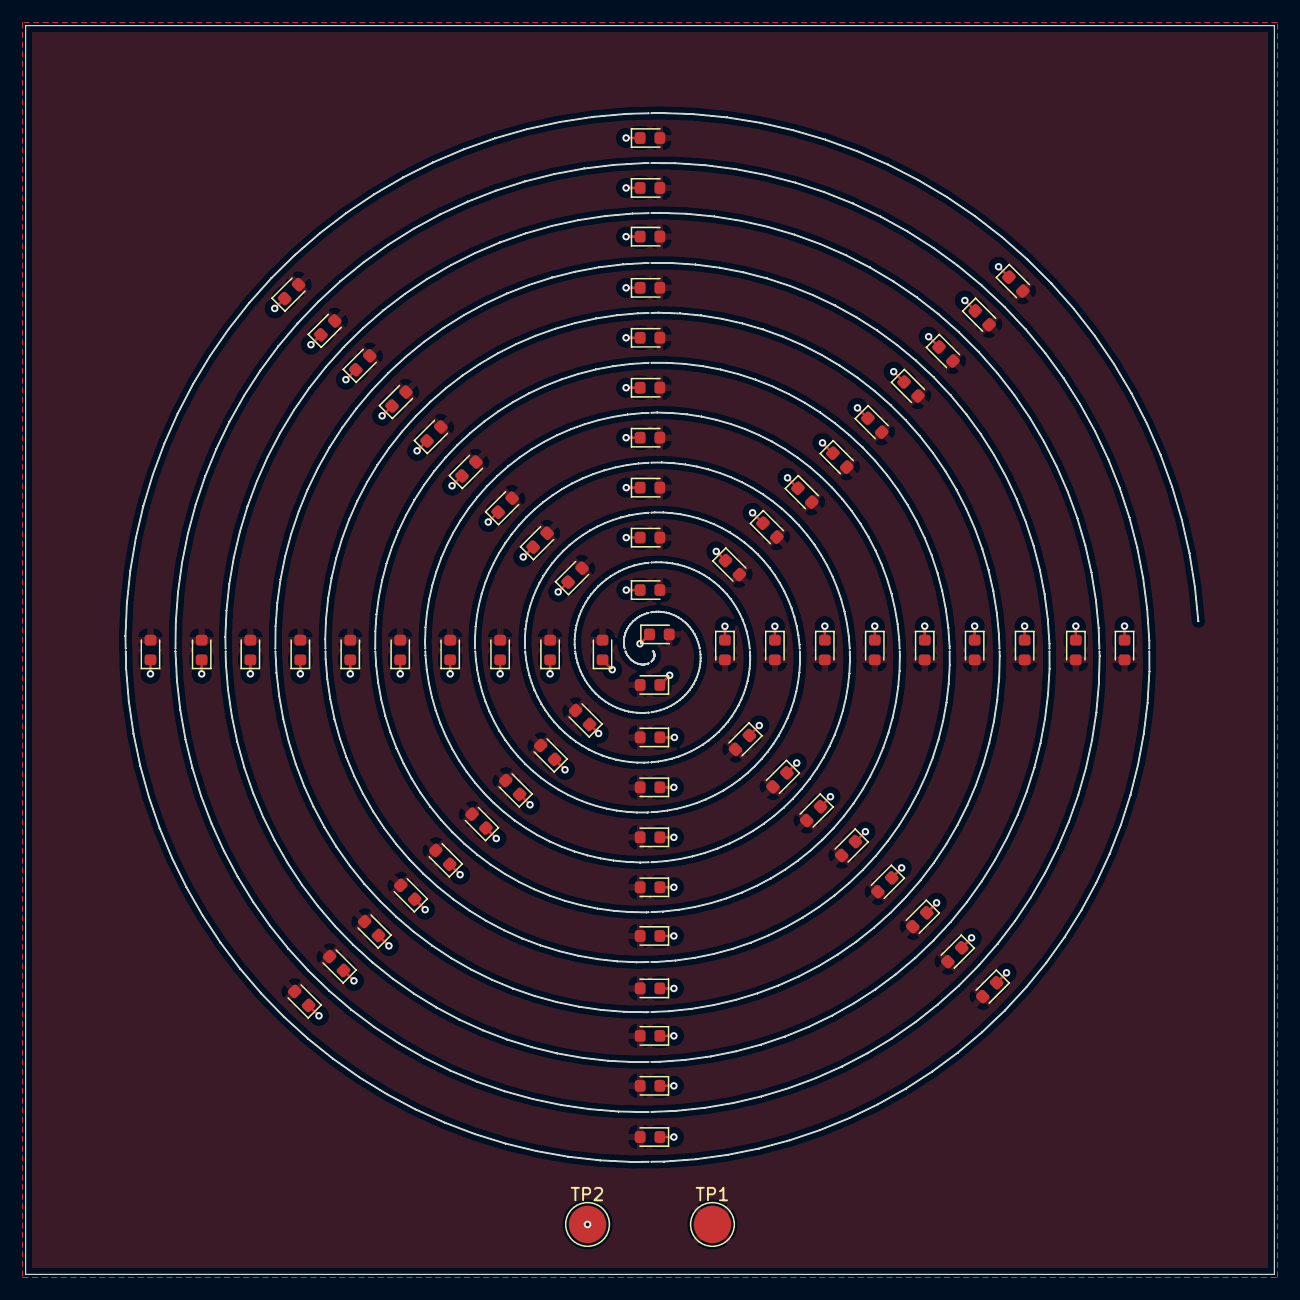
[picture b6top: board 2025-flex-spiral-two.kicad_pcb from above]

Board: 2 copper layers, 100.0 x 100.0 mm, 77 parts (0 on the bottom side), 2 nets.

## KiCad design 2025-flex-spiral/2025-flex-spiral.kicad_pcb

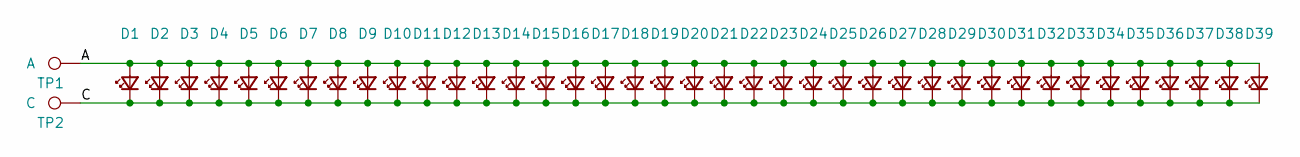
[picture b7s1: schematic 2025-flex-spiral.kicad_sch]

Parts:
D1, D2, D3, D4, D5, D6, D7, D8, D9, D10, D11, D12, D13, D14, D15, D16, D17, D18, D19, D20, D21, D22, D23, D24, D25, D26, D27, D28, D29, D30, D31, D32, D33, D34, D35, D36, D37, D38, D39: led_small; LED_0603_1608Metric
TP1: A; TestPoint_Pad_D3.0mm
TP2: C; TestPoint_Pad_D3.0mm

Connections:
/A: D1.2 (A), D2.2 (A), D3.2 (A), D4.2 (A), D5.2 (A), D6.2 (A), D7.2 (A), D8.2 (A), D9.2 (A), D10.2 (A), D11.2 (A), D12.2 (A), D13.2 (A), D14.2 (A), D15.2 (A), D16.2 (A), D17.2 (A), D18.2 (A), D19.2 (A), D20.2 (A), D21.2 (A), D22.2 (A), D23.2 (A), D24.2 (A), D25.2 (A), D26.2 (A), D27.2 (A), D28.2 (A), D29.2 (A), D30.2 (A), D31.2 (A), D32.2 (A), D33.2 (A), D34.2 (A), D35.2 (A), D36.2 (A), D37.2 (A), D38.2 (A), D39.2 (A), TP1.1
/C: D1.1 (K), D2.1 (K), D3.1 (K), D4.1 (K), D5.1 (K), D6.1 (K), D7.1 (K), D8.1 (K), D9.1 (K), D10.1 (K), D11.1 (K), D12.1 (K), D13.1 (K), D14.1 (K), D15.1 (K), D16.1 (K), D17.1 (K), D18.1 (K), D19.1 (K), D20.1 (K), D21.1 (K), D22.1 (K), D23.1 (K), D24.1 (K), D25.1 (K), D26.1 (K), D27.1 (K), D28.1 (K), D29.1 (K), D30.1 (K), D31.1 (K), D32.1 (K), D33.1 (K), D34.1 (K), D35.1 (K), D36.1 (K), D37.1 (K), D38.1 (K), D39.1 (K), TP2.1

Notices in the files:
micromod-pmod-function/tmp.1/MicroMod_Environmental.kicad_sch:
https://creativecommons.org/licenses/by-sa/4.0
Released under the Creative Commons
parts and their libraries:
Released under the Creative Commons Attribution Share-Alike 4.0 License
